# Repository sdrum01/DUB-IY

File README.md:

# DUB-IY Dub Siren with RP2040 CPU

## Repository to collect electronic and CAD/CAM Stuff

This repository belongs to the project [*DUBSIREN_rp2040*](https://github.com/sdrum01/dubsiren_rp2040), whitch contains the firmware of the DUB-IY.

Dub sirens are simple synthesizers without VCA (Voltage Controlled Amplifier) or VCF (Voltage Controlled Filter), but usually with a VCO (Voltage Controlled Oscillator) modulated by an LFO (Low Frequency Generator).

Such sirens are typically built with analog circuits. The challenge, however, was to optimize the parameter storage of digital solutions, simplify the electronics and to make it hackable.

**DUB-IY** is based on a Raspberry Pi Pico with an RP2040 CPU. It is fast enough to emulate VCOs and LFOs and offers sufficient options for internal data storage.

The Dub siren creates an square wave signal with an adjustable duty cycle. The sound can be modulated by two LFOs and an envelope generator to modulate the timing parameter. 

Finally, the signal is perfected with an integrated echo effect. 

The following values can be adjusted using potentiometers and switches:

* LFO1 waveform
(square, triple square, triangle, sawtooth, pulse)
* LFO2 waveform (square, triangle, sawtooth)
* Oscillator base frequency
* LFO1 and LFO2 frequency
* LFO1 and LFO2 contribution (negative and positive)
* Timing envelope contribution
* Oscillator waveform duty cycle
* LFO start retriggering
* Delay time (echo)
* Feedback (echo)
* Overall volume

The combination of LFOs 1 and 2 already produces many experimental siren sounds,
but the timing envelope adds significantly more dynamics to the sound.

>[!NOTE]
   >
   >This is a non-profit project with no goal of making big money.
   >It's purely for fun, and we assume no liability!
   
## Waiting List

To reserve one device or PCB pls write me an email: dub-iy@sdrum.elementfx.com

## Documentation

Have a look into the short introduction on YouTube:

- [DUB-IY Introduction](https://youtu.be/Yc06HZqR8gg?si=ktLNwQYJj4XRiWYL)

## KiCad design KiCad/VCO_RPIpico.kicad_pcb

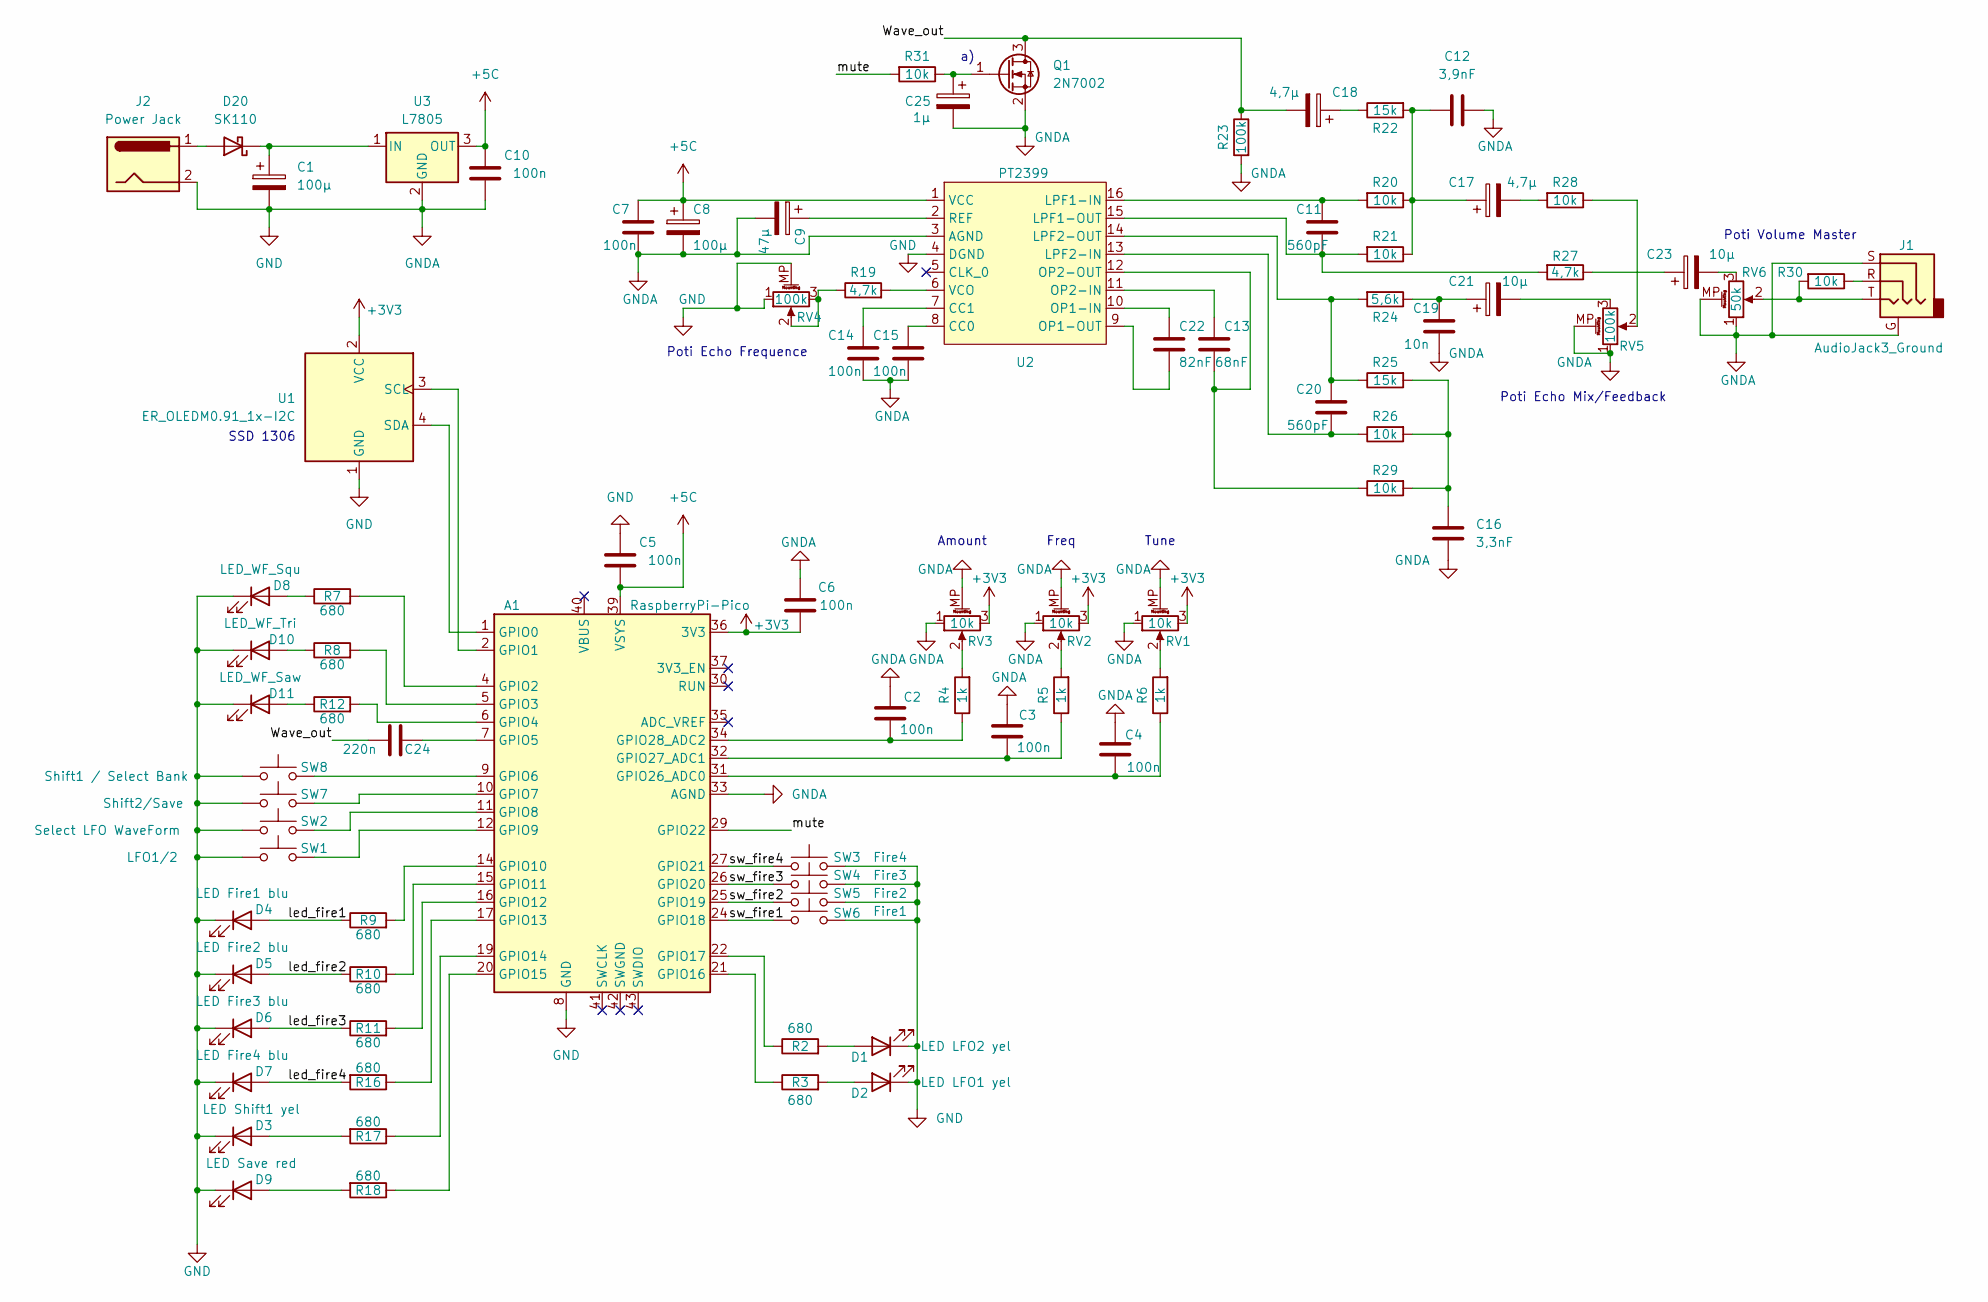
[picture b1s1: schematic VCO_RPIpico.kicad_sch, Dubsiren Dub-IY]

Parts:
A1: RaspberryPi-Pico; RPi_Pico_SMD_TH
C1, C8: 100µ; CP_Elec_6.3x5.8
C2, C3, C4, C5, C6, C7: 100n; C_1206_3216Metric
C9: 47µ; CP_Elec_6.3x5.3
C10, C14, C15: 100n; C_0805_2012Metric_Pad1.18x1.45mm_HandSolder
C11, C20: 560pF; C_0805_2012Metric_Pad1.18x1.45mm_HandSolder
C12: 3,9nF; C_0805_2012Metric_Pad1.18x1.45mm_HandSolder
C13: 68nF; C_0805_2012Metric_Pad1.18x1.45mm_HandSolder
C16: 3,3nF; C_0805_2012Metric_Pad1.18x1.45mm_HandSolder
C17, C18: 4,7µ; CP_Elec_4x5.7
C19: 10n; C_0805_2012Metric_Pad1.18x1.45mm_HandSolder
C21, C23: 10µ; CP_Elec_4x5.7
C22: 82nF; C_0805_2012Metric_Pad1.18x1.45mm_HandSolder
C24: 220n; C_1206_3216Metric
C25: 1µ; CP_Elec_4x5.7
D1: LED LFO2 yel; LED_D3.0mm
D2: LED LFO1 yel; LED_D3.0mm
D3: LED Shift1 yel; LED_D3.0mm
D4: LED Fire1 blu; LED_D3.0mm
D5: LED Fire2 blu; LED_D3.0mm
D6: LED Fire3 blu; LED_D3.0mm
D7: LED Fire4 blu; LED_D3.0mm
D8: LED_WF_Squ; LED_D3.0mm
D9: LED Save red; LED_D3.0mm
D10: LED_WF_Tri; LED_D3.0mm
D11: LED_WF_Saw; LED_D3.0mm
D20: SK110; D_SMA-SMB_Universal_Handsoldering
J1: AudioJack3_Ground; Jack_6.35mm_Neutrik_NMJ6HFD2_Horizontal
J2: Power Jack; BarrelJack_GCT_DCJ200-10-A_Horizontal
Q1: 2N7002; SOT-23
R2, R3, R7, R8, R9, R10, R11, R12, R16, R17, R18: 680; R_1206_3216Metric
R4, R5, R6: 1k; R_1206_3216Metric
R19, R27: 4,7k; R_1206_3216Metric
R20, R21, R26, R28, R29, R30, R31: 10k; R_1206_3216Metric
R22, R25: 15k; R_1206_3216Metric
R23: 100k; R_1206_3216Metric
R24: 5,6k; R_1206_3216Metric
RV1, RV2, RV3: 10k; Potentiometer_Alps_RK09K_Single_Vertical
RV4, RV5: 100k; Potentiometer_Alps_RK09K_Single_Vertical
RV6: 50k; Potentiometer_Alps_RK09K_Single_Vertical
SW1: LFO1/2; SW_PUSH_6mm
SW2: Select LFO WaveForm; SW_PUSH_6mm
SW3: Fire4; SW_PUSH_6mm
SW4: Fire3; SW_PUSH_6mm
SW5: Fire2; SW_PUSH_6mm
SW6: Fire1; SW_PUSH_6mm
SW7: Shift2/Save; SW_PUSH_6mm
SW8: Shift1 / Select Bank; SW_PUSH_6mm
U1: ER_OLEDM0.91_1x-I2C; Adafruit_SSD1306
U2: PT2399; DIP-16_W7.62mm_Socket_LongPads
U3: L7805; TO-252-3_TabPin2

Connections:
+3V3: A1.36 (3V3), C6.2, RV1.3, RV2.3, RV3.3, U1.2 (VCC)
+5C: A1.39 (VSYS), C5.2, C7.1, C8.1, C10.1, U2.1 (VCC), U3.3 (OUT)
/Wave_out: C18.2, C24.1, Q1.3 (D), R23.1
/led_fire1: D4.2 (A), R9.1
/led_fire2: D5.2 (A), R10.1
/led_fire3: D6.2 (A), R11.1
/led_fire4: D7.2 (A), R16.2
/mute: A1.29 (GPIO22), R31.2
/sw_fire1: A1.24 (GPIO18), SW6.1
/sw_fire2: A1.25 (GPIO19), SW5.1
/sw_fire3: A1.26 (GPIO20), SW4.1
/sw_fire4: A1.27 (GPIO21), SW3.1
GND: A1.3 (GND), A1.8 (GND), A1.13 (GND), A1.18 (GND), A1.23 (GND), A1.28 (GND), A1.33 (AGND), A1.38 (GND), C1.2, C2.1, C3.1, C4.1, C5.1, C6.1, C7.2, C8.2, C9.2, C10.2, C12.1, C14.2, C15.2, C16.2, C19.2, C25.2, D1.1 (K), D2.1 (K), D3.1 (K), D4.1 (K), D5.1 (K), D6.1 (K), D7.1 (K), D8.1 (K), D9.1 (K), D10.1 (K), D11.1 (K), J1.G, J1.S, J2.2, Q1.2 (S), R23.2, RV1.1, RV1.MP (MountPin), RV2.1, RV2.MP (MountPin), RV3.1, RV3.MP (MountPin), RV4.1, RV4.MP (MountPin), RV5.1, RV5.MP (MountPin), RV6.1, RV6.MP (MountPin), SW1.1, SW2.1, SW3.2, SW4.2, SW5.2, SW6.2, SW7.1, SW8.1, U1.1 (GND), U2.3 (AGND), U2.4 (DGND), U3.2 (GND)
unnamed: A1.1 (GPIO0), U1.4 (SDA)
unnamed: A1.2 (GPIO1), U1.3 (SCL)
unnamed: A1.4 (GPIO2), R7.2
unnamed: A1.5 (GPIO3), R8.2
unnamed: A1.6 (GPIO4), R12.2
unnamed: A1.7 (GPIO5), C24.2
unnamed: A1.9 (GPIO6), SW8.2
unnamed: A1.10 (GPIO7), SW7.2
unnamed: A1.11 (GPIO8), SW2.2
unnamed: A1.12 (GPIO9), SW1.2
unnamed: A1.14 (GPIO10), R9.2
unnamed: A1.15 (GPIO11), R10.2
unnamed: A1.16 (GPIO12), R11.2
unnamed: A1.17 (GPIO13), R16.1
unnamed: A1.19 (GPIO14), R17.1
unnamed: A1.20 (GPIO15), R18.1
unnamed: A1.21 (GPIO16), R3.1
unnamed: A1.22 (GPIO17), R2.1
unnamed: A1.31 (GPIO26_ADC0), C4.2, R6.1
unnamed: A1.32 (GPIO27_ADC1), C3.2, R5.1
unnamed: A1.34 (GPIO28_ADC2), C2.2, R4.1
unnamed: C12.2, C17.1, R20.1, R21.1, R22.2
unnamed: C16.1, R25.2, R26.2, R29.2
unnamed: C17.2, R28.2
unnamed: C18.1, R22.1
unnamed: C19.1, C21.1, R24.1
unnamed: C21.2, RV5.3
unnamed: C23.1, R27.1
unnamed: C23.2, RV6.3
unnamed: D1.2 (A), R2.2
unnamed: D2.2 (A), R3.2
unnamed: D3.2 (A), R17.2
unnamed: D8.2 (A), R7.1
unnamed: D9.2 (A), R18.2
unnamed: D10.2 (A), R8.1
unnamed: D11.2 (A), R12.1
unnamed: D20.2 (A), J2.1
unnamed: C1.1, D20.1 (K), U3.1 (IN)
unnamed: J1.R, R30.1
unnamed: J1.T, R30.2, RV6.2
unnamed: C25.1, Q1.1 (G), R31.1
unnamed: R4.2, RV3.2
unnamed: R5.2, RV2.2
unnamed: R6.2, RV1.2
unnamed: R19.1, RV4.2, RV4.3
unnamed: R28.1, RV5.2
unnamed: C15.1, U2.8 (CC0)
unnamed: C14.1, U2.7 (CC1)
unnamed: C11.1, R20.2, U2.16 (LPF1-IN)
unnamed: C11.2, R21.2, R27.2, U2.15 (LPF1-OUT)
unnamed: C20.2, R26.1, U2.13 (LPF2-IN)
unnamed: C20.1, R24.2, R25.1, U2.14 (LPF2-OUT)
unnamed: C22.1, U2.10 (OP1-IN)
unnamed: C22.2, U2.9 (OP1-OUT)
unnamed: C13.1, U2.11 (OP2-IN)
unnamed: C13.2, R29.1, U2.12 (OP2-OUT)
unnamed: C9.1, U2.2 (REF)
unnamed: R19.2, U2.6 (VCO)

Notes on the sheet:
Poti Echo Mix/Feedback
SSD 1306
Freq
Poti Echo Frequence
Tune
Poti Volume Master
Amount

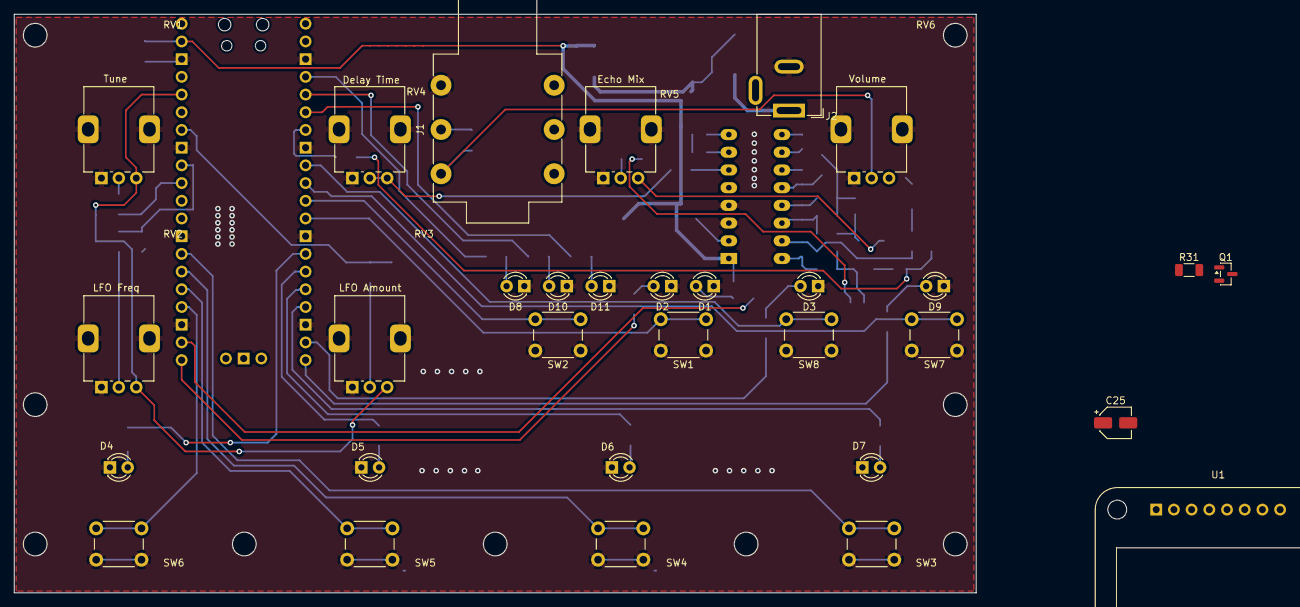
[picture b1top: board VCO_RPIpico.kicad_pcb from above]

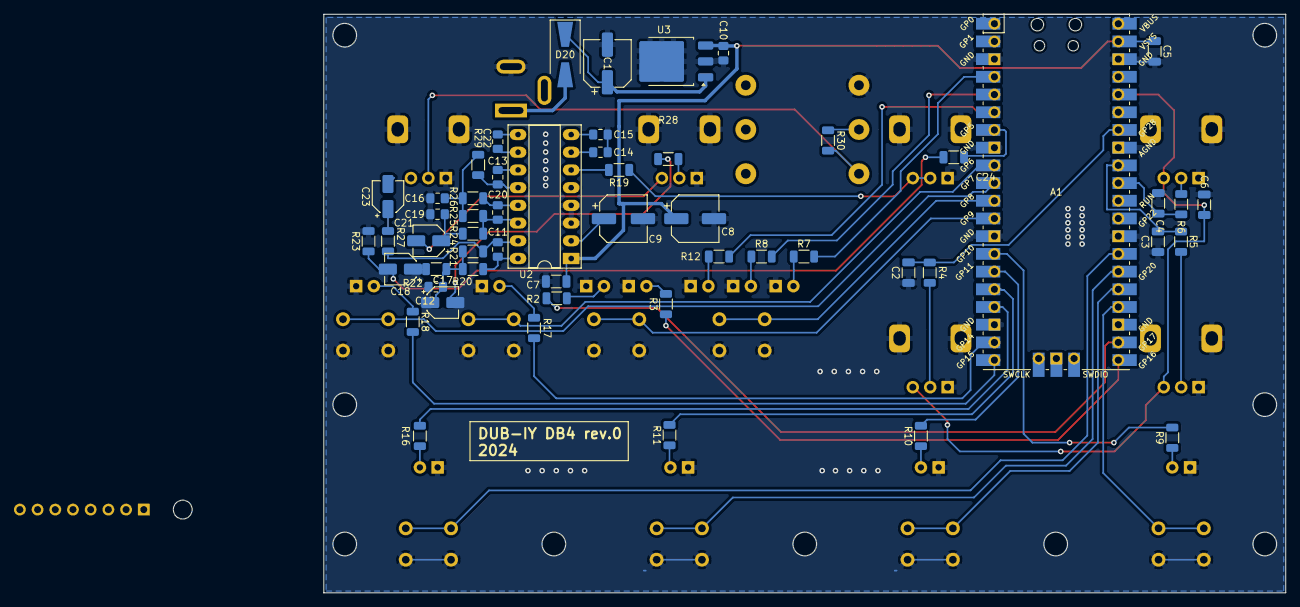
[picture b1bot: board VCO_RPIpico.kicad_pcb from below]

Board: 2 copper layers, 138.0 x 83.0 mm, 85 parts (54 on the bottom side), 71 nets.
